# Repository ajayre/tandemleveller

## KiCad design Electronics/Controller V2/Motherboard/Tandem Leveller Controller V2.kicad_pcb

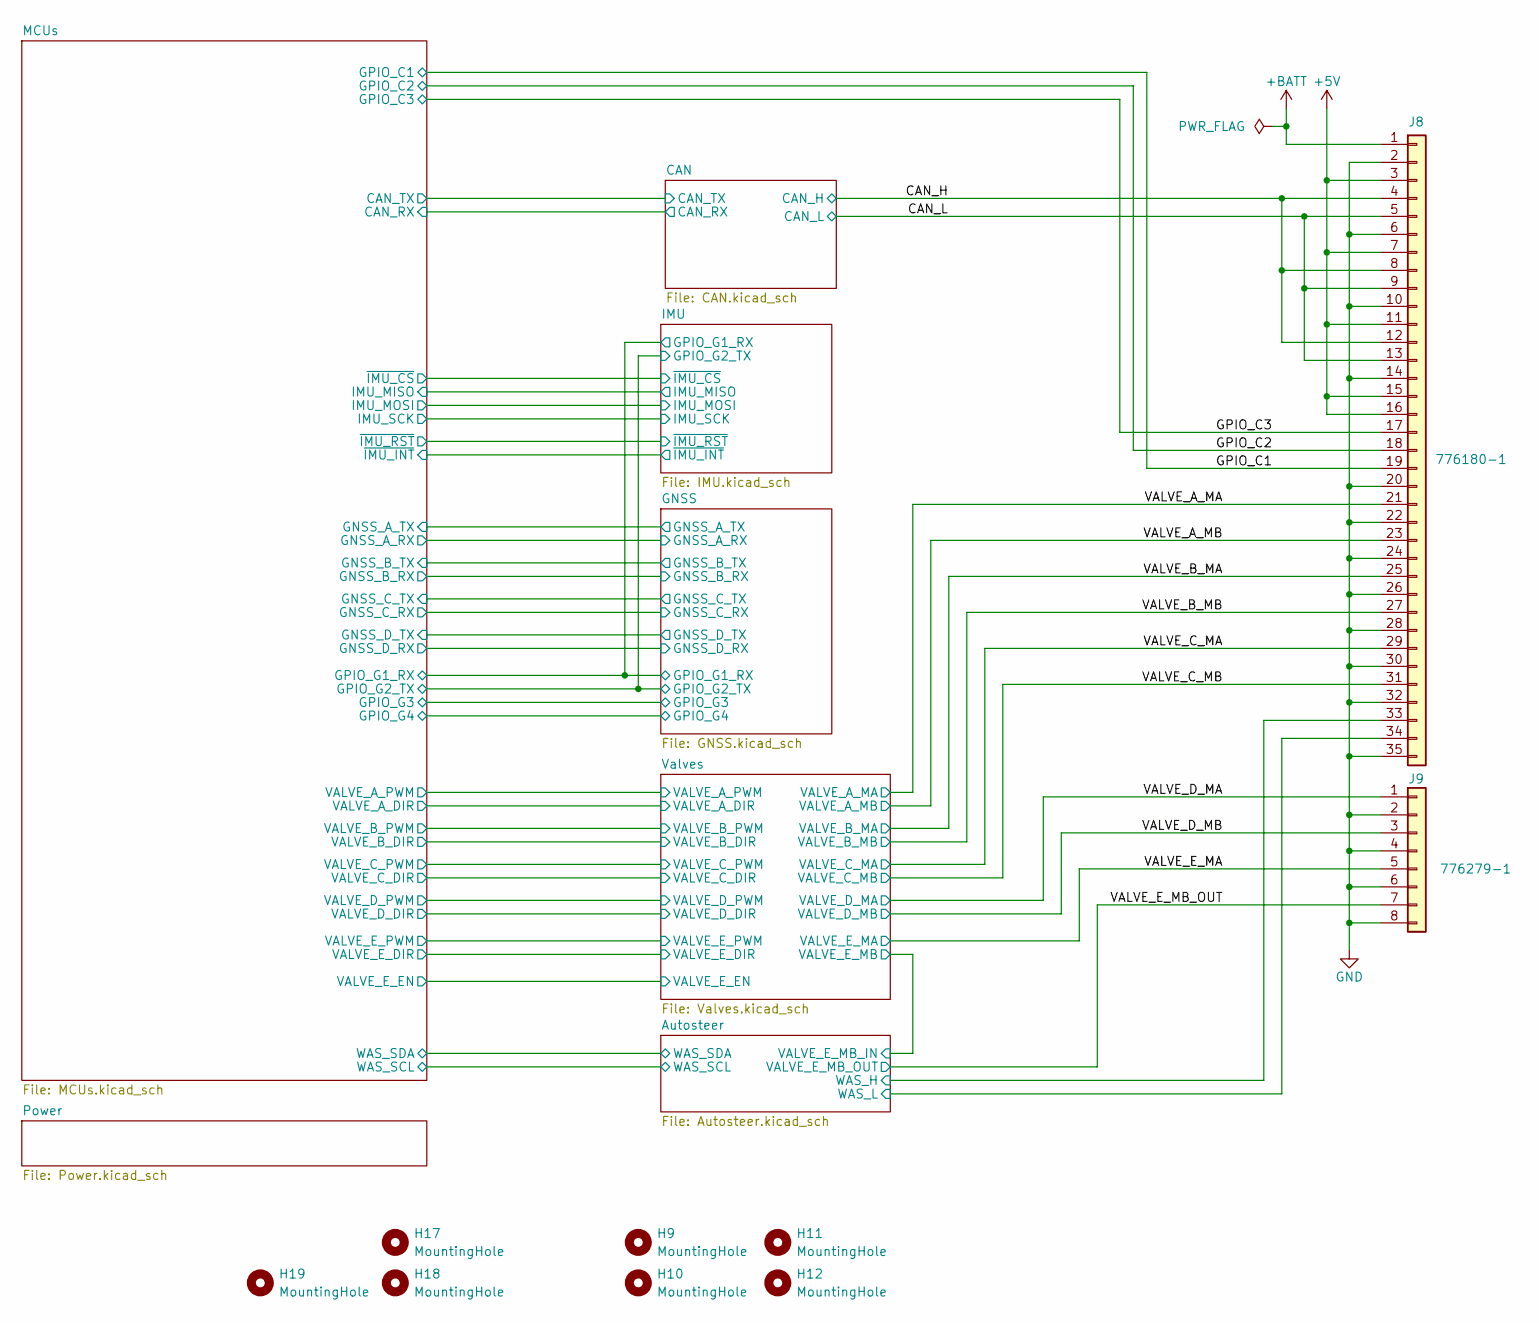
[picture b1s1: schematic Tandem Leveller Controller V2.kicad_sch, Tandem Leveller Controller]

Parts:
H9, H10, H11, H12, H17, H18, H19: MountingHole; MountingHole_4mm
J8: 776180-1; 776180-1 AMPHENOL AMP 35pos
J9: 776279-1; 776279-1 AMPHENOL AMP 8pos

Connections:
+5V: J8.3, J8.7, J8.11, J8.15, J8.16; also elsewhere on the board
+BATT: J8.1; also elsewhere on the board
/Autosteer/WAS_H: J8.33; also elsewhere on the board
/Autosteer/WAS_L: J8.34; also elsewhere on the board
/CAN_H: J8.4, J8.8, J8.12; also elsewhere on the board
/CAN_L: J8.5, J8.9, J8.13; also elsewhere on the board
/GPIO_C1: J8.19; also elsewhere on the board
/GPIO_C2: J8.18; also elsewhere on the board
/GPIO_C3: J8.17; also elsewhere on the board
/VALVE_A_MA: J8.21; also elsewhere on the board
/VALVE_A_MB: J8.23; also elsewhere on the board
/VALVE_B_MA: J8.25; also elsewhere on the board
/VALVE_B_MB: J8.27; also elsewhere on the board
/VALVE_C_MA: J8.29; also elsewhere on the board
/VALVE_C_MB: J8.31; also elsewhere on the board
/VALVE_D_MA: J9.1; also elsewhere on the board
/VALVE_D_MB: J9.3; also elsewhere on the board
/VALVE_E_MA: J9.5; also elsewhere on the board
/VALVE_E_MB_OUT: J9.7; also elsewhere on the board
GND: J8.2, J8.6, J8.10, J8.14, J8.20, J8.22, J8.24, J8.26, J8.28, J8.30, J8.32, J8.35, J9.2, J9.4, J9.6, J9.8; also elsewhere on the board

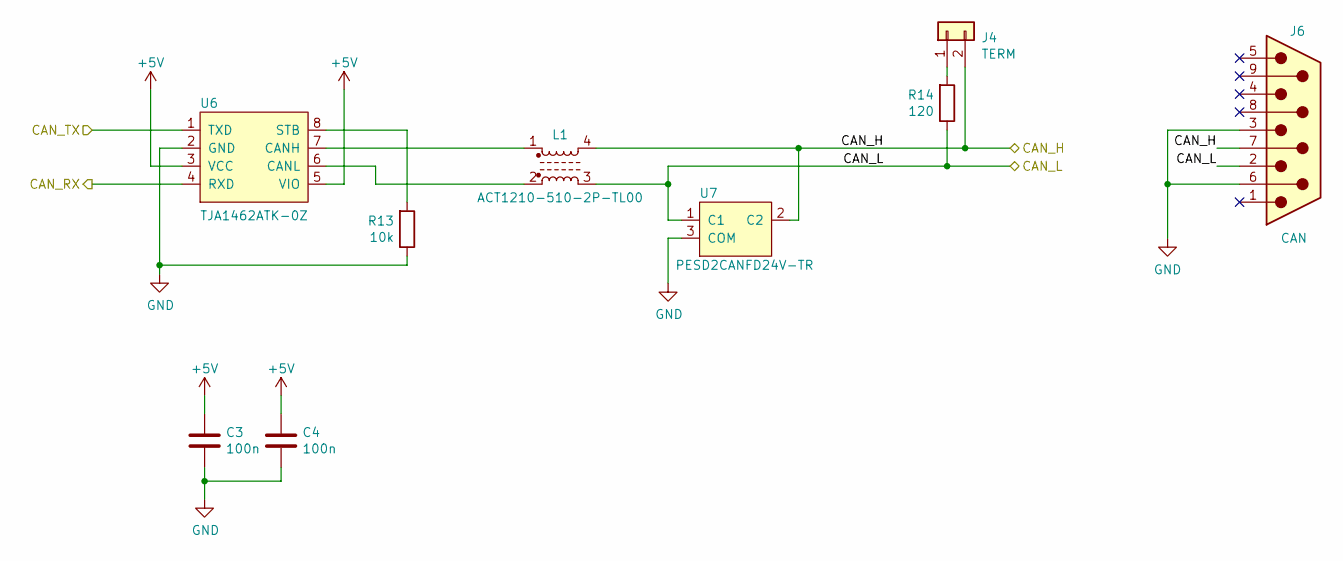
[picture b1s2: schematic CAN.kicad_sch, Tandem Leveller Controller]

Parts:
C3, C4: 100n; C_0805_2012Metric; LCSC C1711
J4: TERM; PinHeader_1x02_P2.54mm_Vertical; LCSC C7494857
J6: CAN; DSUB-9_Male_Vertical_P2.77x2.84mm
L1: ACT1210-510-2P-TL00; LCSC C95572
R13: 10k; R_0805_2012Metric; LCSC C17414
R14: 120; R_0805_2012Metric; LCSC C17437
U6: TJA1462ATK-0Z; HVSON8_0_65mm; LCSC C3229259
U7: PESD2CANFD24V-TR; SOT-23; LCSC C552486

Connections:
+5V: C3.1, C4.1, U6.3 (VCC), U6.5 (VIO); also elsewhere on the board
/CAN/CAN_RX: U6.4 (RXD); also elsewhere on the board
/CAN/CAN_TX: U6.1 (TXD); also elsewhere on the board
/CAN_H: J4.2, J6.7, L1.4, U7.2 (C2); also elsewhere on the board
/CAN_L: J6.2, L1.3, R14.1, U7.1 (C1); also elsewhere on the board
GND: C3.2, C4.2, J6.3, J6.6, R13.1, U6.2 (GND), U7.3 (COM); also elsewhere on the board
unnamed: J4.1, R14.2
unnamed: L1.1, U6.7 (CANH)
unnamed: L1.2, U6.6 (CANL)
unnamed: R13.2, U6.8 (STB)

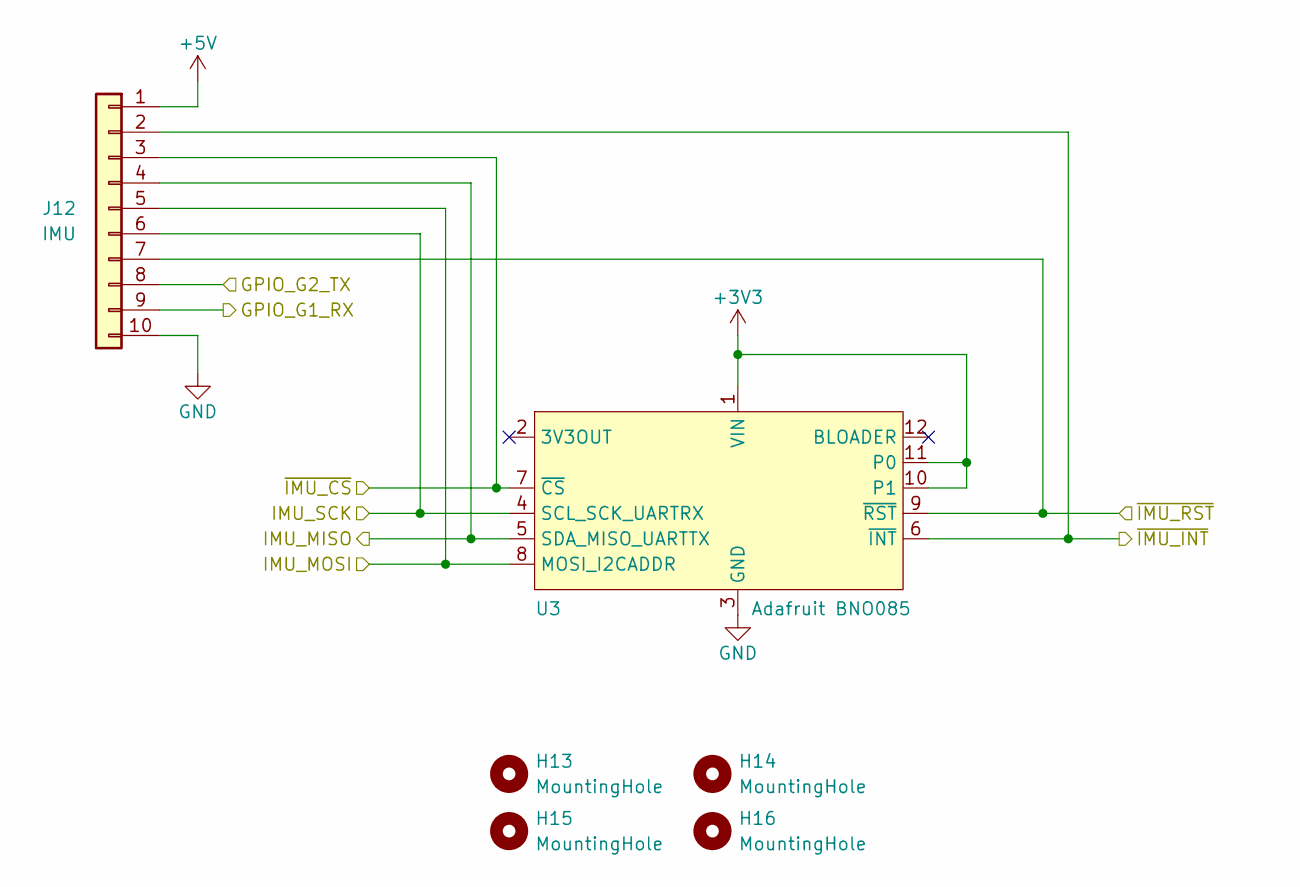
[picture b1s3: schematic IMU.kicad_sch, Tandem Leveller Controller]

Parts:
H13, H14, H15, H16: MountingHole; MountingHole_3.2mm_M3
J12: IMU; JST_PH_B10B-PH-K_1x10_P2.00mm_Vertical
U3: Adafruit BNO085; Adafruit_BNO085

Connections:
+3V3: U3.1 (VIN), U3.10 (P1), U3.11 (P0); also elsewhere on the board
+5V: J12.1; also elsewhere on the board
/GNSS/GPIO_G1: J12.9; also elsewhere on the board
/GNSS/GPIO_G2: J12.8; also elsewhere on the board
/IMU/IMU_MISO: J12.4, U3.5 (SDA_MISO_UARTTX); also elsewhere on the board
/IMU/IMU_MOSI: J12.5, U3.8 (MOSI_I2CADDR); also elsewhere on the board
/IMU/IMU_SCK: J12.6, U3.4 (SCL_SCK_UARTRX); also elsewhere on the board
/IMU/~IMU_CS: J12.3, U3.7 (~CS); also elsewhere on the board
/IMU/~IMU_INT: J12.2, U3.6 (~INT); also elsewhere on the board
/IMU/~IMU_RST: J12.7, U3.9 (~RST); also elsewhere on the board
GND: J12.10, U3.3 (GND); also elsewhere on the board

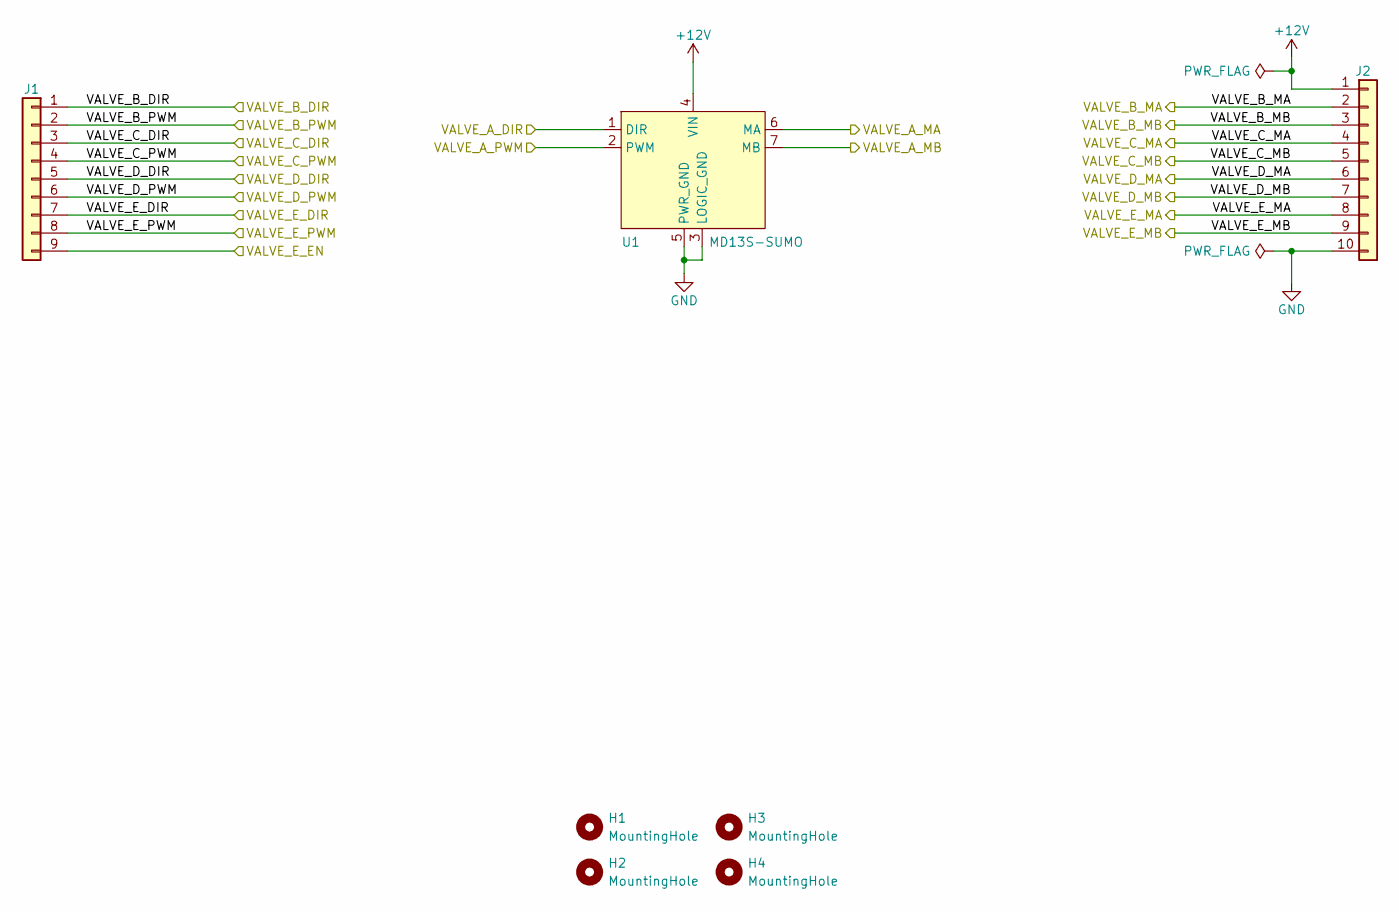
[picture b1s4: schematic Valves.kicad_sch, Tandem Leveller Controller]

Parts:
H1, H2, H3, H4: MountingHole; MountingHole_6.4mm_M6
J1: Conn_01x08; JST_PH_B9B-PH-K_1x09_P2.00mm_Vertical
J2: Conn_01x10; JST_XH_B10B-XH-A_1x10_P2.50mm_Vertical
U1: MD13S-SUMO

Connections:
+12V: J2.1, U1.4 (VIN); also elsewhere on the board
/MCUs/VALVE_A_DIR: U1.1 (DIR); also elsewhere on the board
/MCUs/VALVE_A_PWM: U1.2 (PWM); also elsewhere on the board
/MCUs/VALVE_E_EN: J1.9; also elsewhere on the board
/VALVE_A_MA: U1.6 (MA); also elsewhere on the board
/VALVE_A_MB: U1.7 (MB); also elsewhere on the board
/VALVE_B_MA: J2.2; also elsewhere on the board
/VALVE_B_MB: J2.3; also elsewhere on the board
/VALVE_C_MA: J2.4; also elsewhere on the board
/VALVE_C_MB: J2.5; also elsewhere on the board
/VALVE_D_MA: J2.6; also elsewhere on the board
/VALVE_D_MB: J2.7; also elsewhere on the board
/VALVE_E_MA: J2.8; also elsewhere on the board
/Valves/VALVE_B_DIR: J1.1; also elsewhere on the board
/Valves/VALVE_B_PWM: J1.2; also elsewhere on the board
/Valves/VALVE_C_DIR: J1.3; also elsewhere on the board
/Valves/VALVE_C_PWM: J1.4; also elsewhere on the board
/Valves/VALVE_D_DIR: J1.5; also elsewhere on the board
/Valves/VALVE_D_PWM: J1.6; also elsewhere on the board
/Valves/VALVE_E_DIR: J1.7; also elsewhere on the board
/Valves/VALVE_E_MB: J2.9; also elsewhere on the board
/Valves/VALVE_E_PWM: J1.8; also elsewhere on the board
GND: J2.10, U1.3 (LOGIC_GND), U1.5 (PWR_GND); also elsewhere on the board

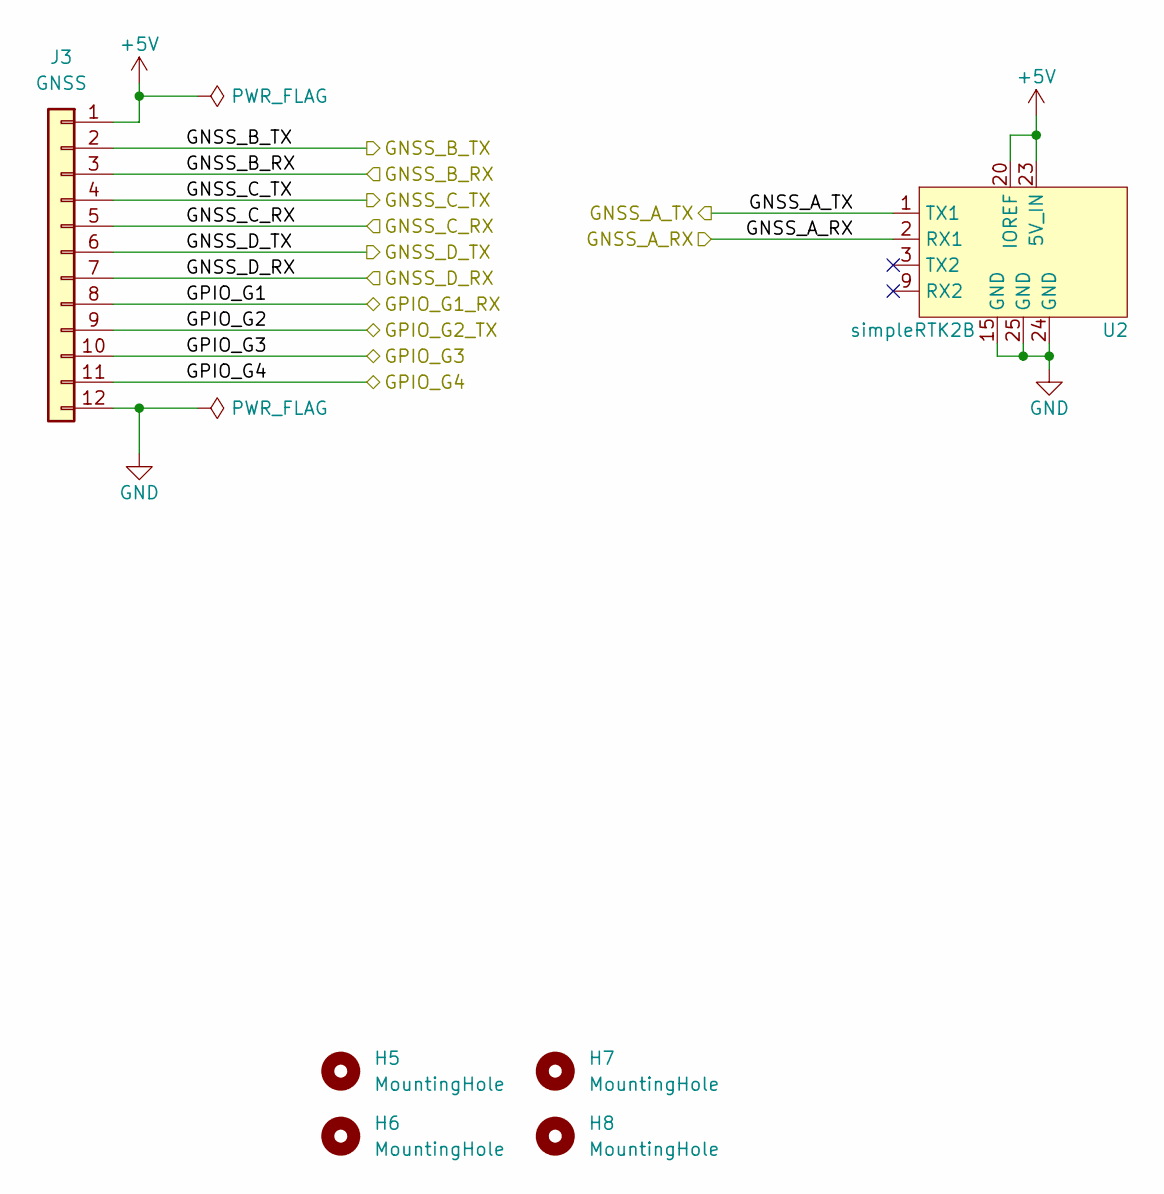
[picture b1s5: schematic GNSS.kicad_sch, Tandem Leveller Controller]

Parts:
H5, H6, H7, H8: MountingHole; MountingHole_6.4mm_M6
J3: GNSS; JST_PH_B12B-PH-K_1x12_P2.00mm_Vertical
U2: simpleRTK2B

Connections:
+5V: J3.1, U2.20 (IOREF), U2.23 (5V_IN); also elsewhere on the board
/GNSS/GNSS_A_RX: U2.2 (RX1); also elsewhere on the board
/GNSS/GNSS_A_TX: U2.1 (TX1); also elsewhere on the board
/GNSS/GNSS_B_RX: J3.3; also elsewhere on the board
/GNSS/GNSS_B_TX: J3.2; also elsewhere on the board
/GNSS/GNSS_C_RX: J3.5; also elsewhere on the board
/GNSS/GNSS_C_TX: J3.4; also elsewhere on the board
/GNSS/GNSS_D_RX: J3.7; also elsewhere on the board
/GNSS/GNSS_D_TX: J3.6; also elsewhere on the board
/GNSS/GPIO_G1: J3.8; also elsewhere on the board
/GNSS/GPIO_G2: J3.9; also elsewhere on the board
/GNSS/GPIO_G3: J3.10; also elsewhere on the board
/GNSS/GPIO_G4: J3.11; also elsewhere on the board
GND: J3.12, U2.15 (GND), U2.24 (GND), U2.25 (GND); also elsewhere on the board

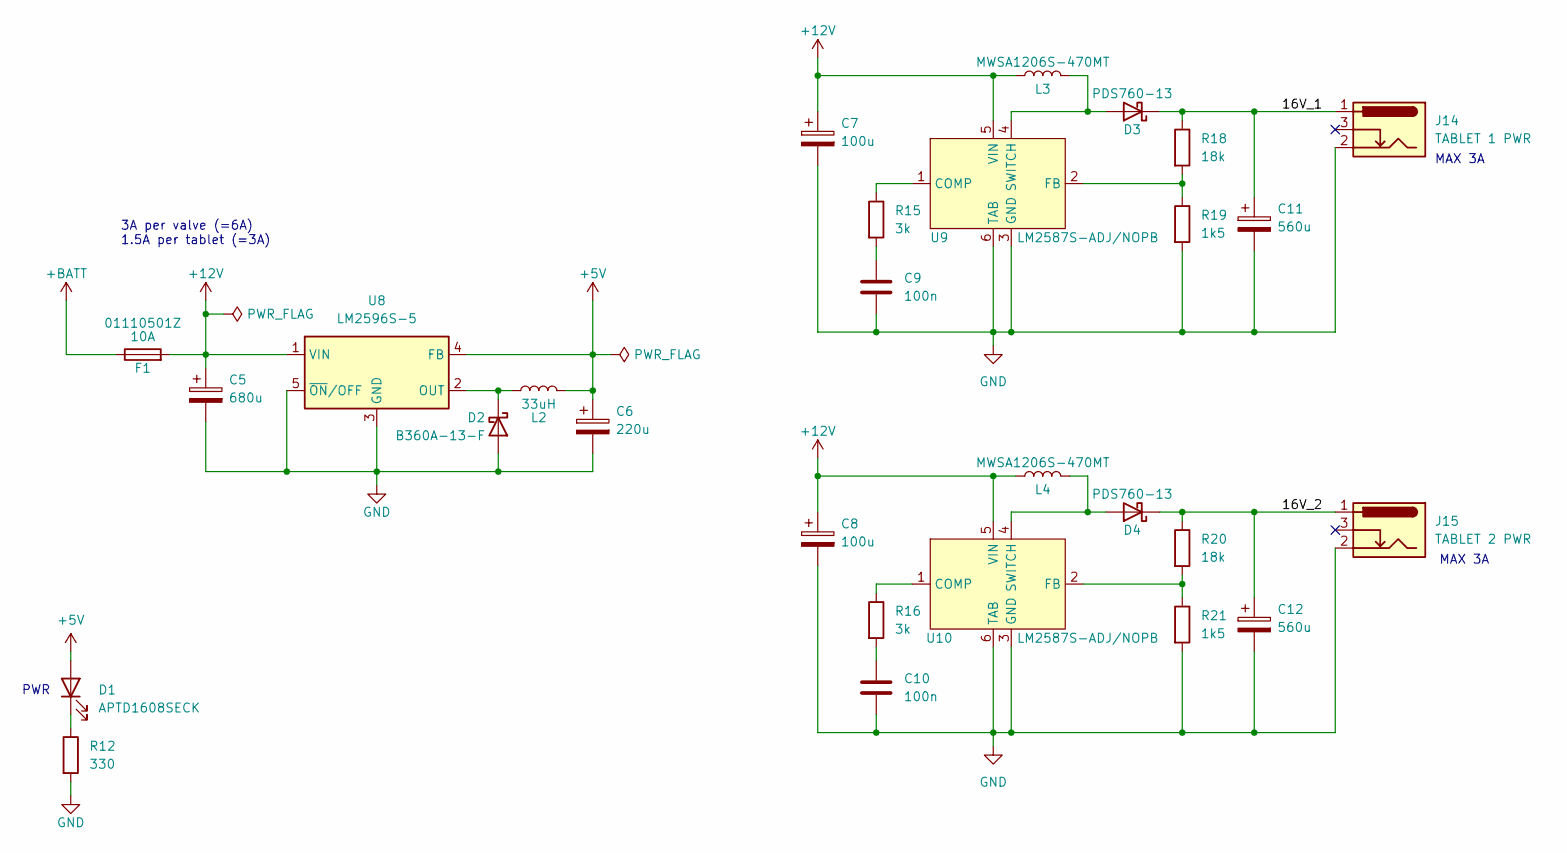
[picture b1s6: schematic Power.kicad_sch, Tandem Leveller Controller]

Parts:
C5: 680u; CP_Elec_10x10.5; LCSC C50456
C6: 220u; CP_Elec_8x6.5; LCSC C3340
C7, C8: 100u; CP_Elec_6.3x5.9; LCSC C340733
C9, C10: 100n; C_0805_2012Metric; LCSC C1711
C11, C12: 560u; CP_Elec_10x10.5; LCSC C1984785
D1: APTD1608SECK; D_0603_1608Metric; LCSC C5879220
D2: B360A-13-F; D_SMA; LCSC C6807778
D3, D4: PDS760-13; D_PowerDI-5; LCSC C3018534
F1: 10A; 5x20 Fuse Holder; LCSC C151075
J14: TABLET 1 PWR; BarrelJack_Wuerth_6941xx301002; LCSC C5441017
J15: TABLET 2 PWR; BarrelJack_Wuerth_6941xx301002; LCSC C5441017
L2: 33uH; MWSA0603S-330MT; LCSC C408454
L3, L4: MWSA1206S-470MT; LCSC C408531
R12: 330; R_0805_2012Metric; LCSC C17630
R15, R16: 3k; R_0805_2012Metric; LCSC C17661
R18, R20: 18k; R_0805_2012Metric; LCSC C17506
R19, R21: 1k5; R_0805_2012Metric; LCSC C4310
U8: LM2596S-5; TO-263-5_TabPin3; LCSC C5276750
U9, U10: LM2587S-ADJ/NOPB; TO-263-5_TabPin6; LCSC C1355343

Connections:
+5V: C6.1, D1.2 (A), L2.2, U8.4 (FB); also elsewhere on the board
+12V: C5.1, C7.1, C8.1, F1.2, L3.1, L4.1, U8.1 (VIN), U9.5 (VIN), U10.5 (VIN); also elsewhere on the board
+BATT: F1.1; also elsewhere on the board
/Power/16V_1: C11.1, D3.1 (K), J14.1, R18.1
/Power/16V_2: C12.1, D4.1 (K), J15.1, R20.1
GND: C5.2, C6.2, C7.2, C8.2, C9.2, C10.2, C11.2, C12.2, D2.2 (A), J14.2, J15.2, R12.2, R19.2, R21.2, U8.3 (GND), U8.5 (~ON/OFF), U9.3 (GND), U9.6 (TAB), U10.3 (GND), U10.6 (TAB); also elsewhere on the board
unnamed: C9.1, R15.2
unnamed: C10.1, R16.2
unnamed: D1.1 (K), R12.1
unnamed: D2.1 (K), L2.1, U8.2 (OUT)
unnamed: D3.2 (A), L3.2, U9.4 (SWITCH)
unnamed: D4.2 (A), L4.2, U10.4 (SWITCH)
unnamed: R15.1, U9.1 (COMP)
unnamed: R18.2, R19.1, U9.2 (FB)
unnamed: R16.1, U10.1 (COMP)
unnamed: R20.2, R21.1, U10.2 (FB)

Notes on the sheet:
PWR
3A per valve (=6A) 1.5A per tablet (=3A)
MAX 3A

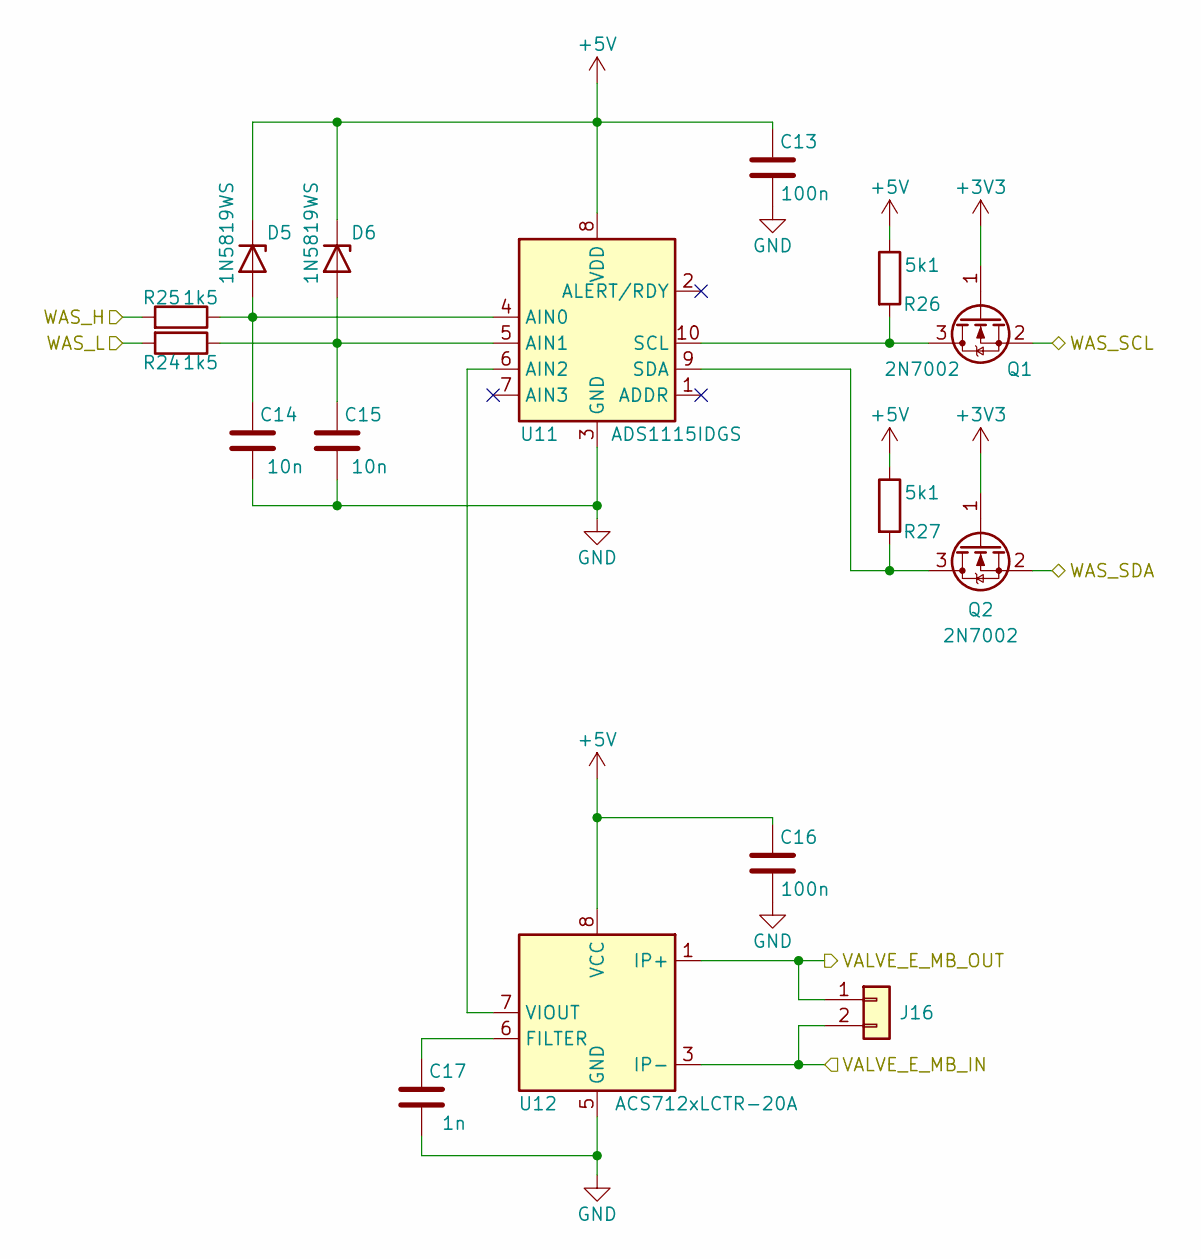
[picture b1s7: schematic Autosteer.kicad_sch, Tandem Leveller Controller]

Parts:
C13, C16: 100n; C_0805_2012Metric; LCSC C1711
C14, C15: 10n; C_0805_2012Metric
C17: 1n; C_0805_2012Metric
D5, D6: 1N5819WS; D_SOD-323; LCSC C191023
J16: PinHeader_1x02_P2.54mm_Vertical; LCSC C7494857
Q1, Q2: 2N7002; SOT-23
R24, R25: 1k5; R_0805_2012Metric
R26, R27: 5k1; R_0805_2012Metric
U11: ADS1115IDGS; TSSOP-10_3x3mm_P0.5mm
U12: ACS712xLCTR-20A; SOIC-8_3.9x4.9mm_P1.27mm

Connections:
+3V3: Q1.1 (G), Q2.1 (G); also elsewhere on the board
+5V: C13.2, C16.2, D5.1 (K), D6.1 (K), R26.1, R27.1, U11.8 (VDD), U12.8 (VCC); also elsewhere on the board
/Autosteer/WAS_H: R25.2; also elsewhere on the board
/Autosteer/WAS_L: R24.2; also elsewhere on the board
/Autosteer/WAS_SCL: Q1.2 (S); also elsewhere on the board
/Autosteer/WAS_SDA: Q2.2 (S); also elsewhere on the board
/VALVE_E_MB_OUT: J16.1, U12.1 (IP+), U12.2 (IP+); also elsewhere on the board
/Valves/VALVE_E_MB: J16.2, U12.3 (IP-), U12.4 (IP-); also elsewhere on the board
GND: C13.1, C14.1, C15.1, C16.1, C17.1, U11.3 (GND), U12.5 (GND); also elsewhere on the board
unnamed: C14.2, D5.2 (A), R25.1, U11.4 (AIN0)
unnamed: C15.2, D6.2 (A), R24.1, U11.5 (AIN1)
unnamed: Q1.3 (D), R26.2, U11.10 (SCL)
unnamed: Q2.3 (D), R27.2, U11.9 (SDA)
unnamed: U11.6 (AIN2), U12.7 (VIOUT)
unnamed: C17.2, U12.6 (FILTER)

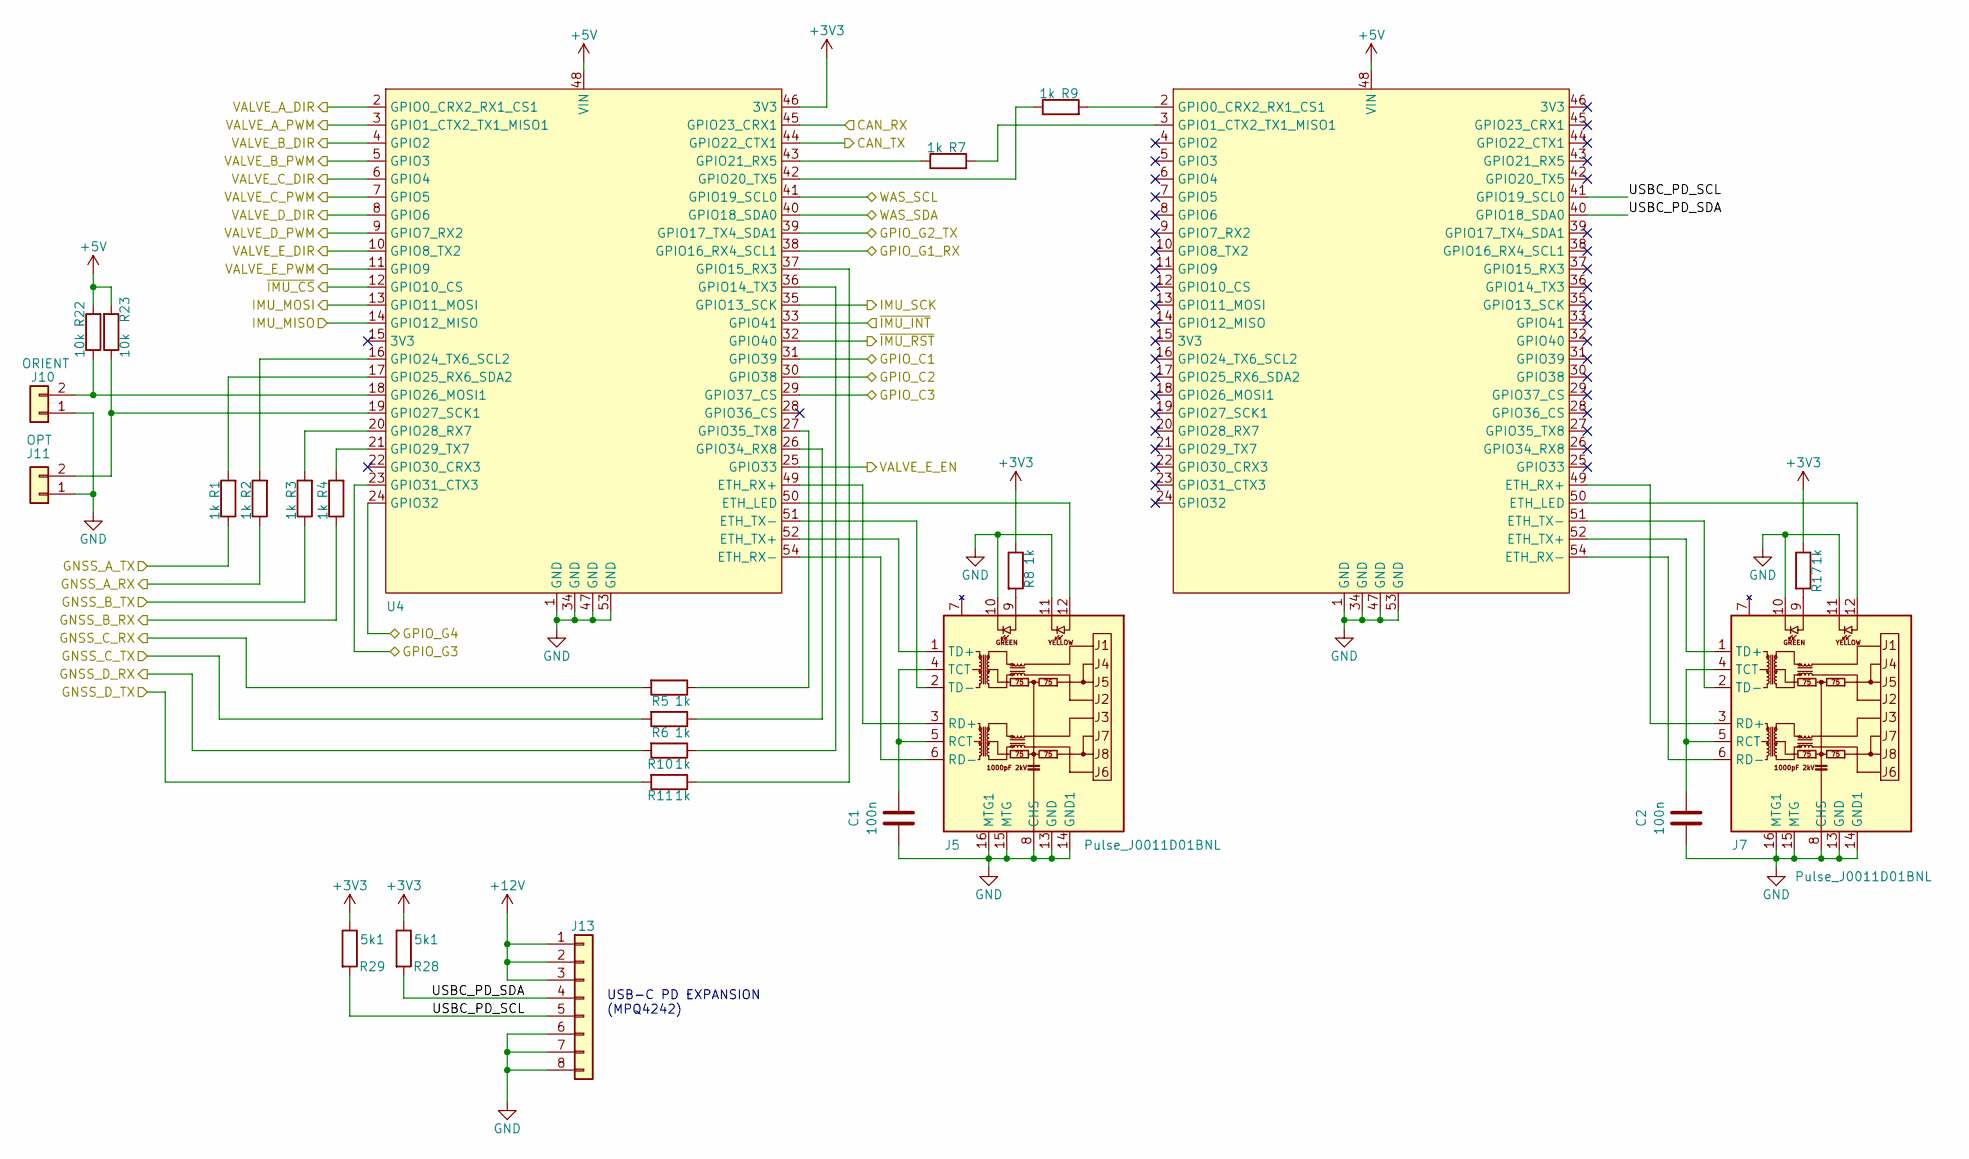
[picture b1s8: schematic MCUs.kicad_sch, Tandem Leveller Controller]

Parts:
C1, C2: 100n; C_0805_2012Metric; LCSC C1711
J5, J7: Pulse_J0011D01BNL; LCSC C581368
J10: ORIENT; PinHeader_1x02_P2.54mm_Vertical; LCSC C7494857
J11: OPT; PinHeader_1x02_P2.54mm_Vertical; LCSC C7494857
J13: Conn_01x10; JST_XH_B8B-XH-A_1x08_P2.50mm_Vertical
R1, R2, R3, R4, R5, R6, R7, R8, R9, R10, R11, R17: 1k; R_0805_2012Metric; LCSC C17513
R22, R23: 10k; R_0805_2012Metric; LCSC C17513
R28, R29: 5k1; R_0805_2012Metric
U4, U5: Teensy_4.1

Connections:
+3V3: R8.1, R17.1, R28.1, R29.1, U4.46 (3V3); also elsewhere on the board
+5V: R22.2, R23.2, U4.48 (VIN), U5.48 (VIN); also elsewhere on the board
+12V: J13.1, J13.2, J13.3; also elsewhere on the board
/Autosteer/WAS_SCL: U4.41 (GPIO19_SCL0); also elsewhere on the board
/Autosteer/WAS_SDA: U4.40 (GPIO18_SDA0); also elsewhere on the board
/CAN/CAN_RX: U4.45 (GPIO23_CRX1); also elsewhere on the board
/CAN/CAN_TX: U4.44 (GPIO22_CTX1); also elsewhere on the board
/GNSS/GNSS_A_RX: R2.1; also elsewhere on the board
/GNSS/GNSS_A_TX: R1.1; also elsewhere on the board
/GNSS/GNSS_B_RX: R4.1; also elsewhere on the board
/GNSS/GNSS_B_TX: R3.1; also elsewhere on the board
/GNSS/GNSS_C_RX: R5.2; also elsewhere on the board
/GNSS/GNSS_C_TX: R6.2; also elsewhere on the board
/GNSS/GNSS_D_RX: R10.2; also elsewhere on the board
/GNSS/GNSS_D_TX: R11.2; also elsewhere on the board
/GNSS/GPIO_G1: U4.38 (GPIO16_RX4_SCL1); also elsewhere on the board
/GNSS/GPIO_G2: U4.39 (GPIO17_TX4_SDA1); also elsewhere on the board
/GNSS/GPIO_G3: U4.23 (GPIO31_CTX3); also elsewhere on the board
/GNSS/GPIO_G4: U4.24 (GPIO32); also elsewhere on the board
/GPIO_C1: U4.31 (GPIO39); also elsewhere on the board
/GPIO_C2: U4.30 (GPIO38); also elsewhere on the board
/GPIO_C3: U4.29 (GPIO37_CS); also elsewhere on the board
/IMU/IMU_MISO: U4.14 (GPIO12_MISO); also elsewhere on the board
/IMU/IMU_MOSI: U4.13 (GPIO11_MOSI); also elsewhere on the board
/IMU/IMU_SCK: U4.35 (GPIO13_SCK); also elsewhere on the board
/IMU/~IMU_CS: U4.12 (GPIO10_CS); also elsewhere on the board
/IMU/~IMU_INT: U4.33 (GPIO41); also elsewhere on the board
/IMU/~IMU_RST: U4.32 (GPIO40); also elsewhere on the board
/MCUs/USBC_PD_SCL: J13.5, R29.2, U5.41 (GPIO19_SCL0)
/MCUs/USBC_PD_SDA: J13.4, R28.2, U5.40 (GPIO18_SDA0)
/MCUs/VALVE_A_DIR: U4.2 (GPIO0_CRX2_RX1_CS1); also elsewhere on the board
/MCUs/VALVE_A_PWM: U4.3 (GPIO1_CTX2_TX1_MISO1); also elsewhere on the board
/MCUs/VALVE_E_EN: U4.25 (GPIO33); also elsewhere on the board
/Valves/VALVE_B_DIR: U4.4 (GPIO2); also elsewhere on the board
/Valves/VALVE_B_PWM: U4.5 (GPIO3); also elsewhere on the board
/Valves/VALVE_C_DIR: U4.6 (GPIO4); also elsewhere on the board
/Valves/VALVE_C_PWM: U4.7 (GPIO5); also elsewhere on the board
/Valves/VALVE_D_DIR: U4.8 (GPIO6); also elsewhere on the board
/Valves/VALVE_D_PWM: U4.9 (GPIO7_RX2); also elsewhere on the board
/Valves/VALVE_E_DIR: U4.10 (GPIO8_TX2); also elsewhere on the board
/Valves/VALVE_E_PWM: U4.11 (GPIO9); also elsewhere on the board
GND: C1.1, C2.1, J5.8 (CHS), J5.10, J5.11, J5.13 (GND), J5.14 (GND1), J5.15 (MTG), J5.16 (MTG1), J7.8 (CHS), J7.10, J7.11, J7.13 (GND), J7.14 (GND1), J7.15 (MTG), J7.16 (MTG1), J10.1, J11.1, J13.6, J13.7, J13.8, U4.1 (GND), U4.34 (GND), U4.47 (GND), U4.53 (GND), U5.1 (GND), U5.34 (GND), U5.47 (GND), U5.53 (GND); also elsewhere on the board
unnamed: J5.9, R8.2
unnamed: C1.2, J5.4 (TCT), J5.5 (RCT)
unnamed: J5.3 (RD+), U4.49 (ETH_RX+)
unnamed: J5.6 (RD-), U4.54 (ETH_RX-)
unnamed: J5.1 (TD+), U4.52 (ETH_TX+)
unnamed: J5.2 (TD-), U4.51 (ETH_TX-)
unnamed: J7.9, R17.2
unnamed: C2.2, J7.4 (TCT), J7.5 (RCT)
unnamed: J7.3 (RD+), U5.49 (ETH_RX+)
unnamed: J7.6 (RD-), U5.54 (ETH_RX-)
unnamed: J7.1 (TD+), U5.52 (ETH_TX+)
unnamed: J7.2 (TD-), U5.51 (ETH_TX-)
unnamed: J10.2, R22.1, U4.18 (GPIO26_MOSI1)
unnamed: J11.2, R23.1, U4.19 (GPIO27_SCK1)
unnamed: J5.12, U4.50 (ETH_LED)
unnamed: R10.1, U4.36 (GPIO14_TX3)
unnamed: R11.1, U4.37 (GPIO15_RX3)
unnamed: R9.1, U4.42 (GPIO20_TX5)
unnamed: R7.1, U4.43 (GPIO21_RX5)
unnamed: R2.2, U4.16 (GPIO24_TX6_SCL2)
unnamed: R1.2, U4.17 (GPIO25_RX6_SDA2)
unnamed: R3.2, U4.20 (GPIO28_RX7)
unnamed: R4.2, U4.21 (GPIO29_TX7)
unnamed: R6.1, U4.26 (GPIO34_RX8)
unnamed: R5.1, U4.27 (GPIO35_TX8)
unnamed: J7.12, U5.50 (ETH_LED)
unnamed: R9.2, U5.2 (GPIO0_CRX2_RX1_CS1)
unnamed: R7.2, U5.3 (GPIO1_CTX2_TX1_MISO1)

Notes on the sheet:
USB-C PD EXPANSION (MPQ4242)

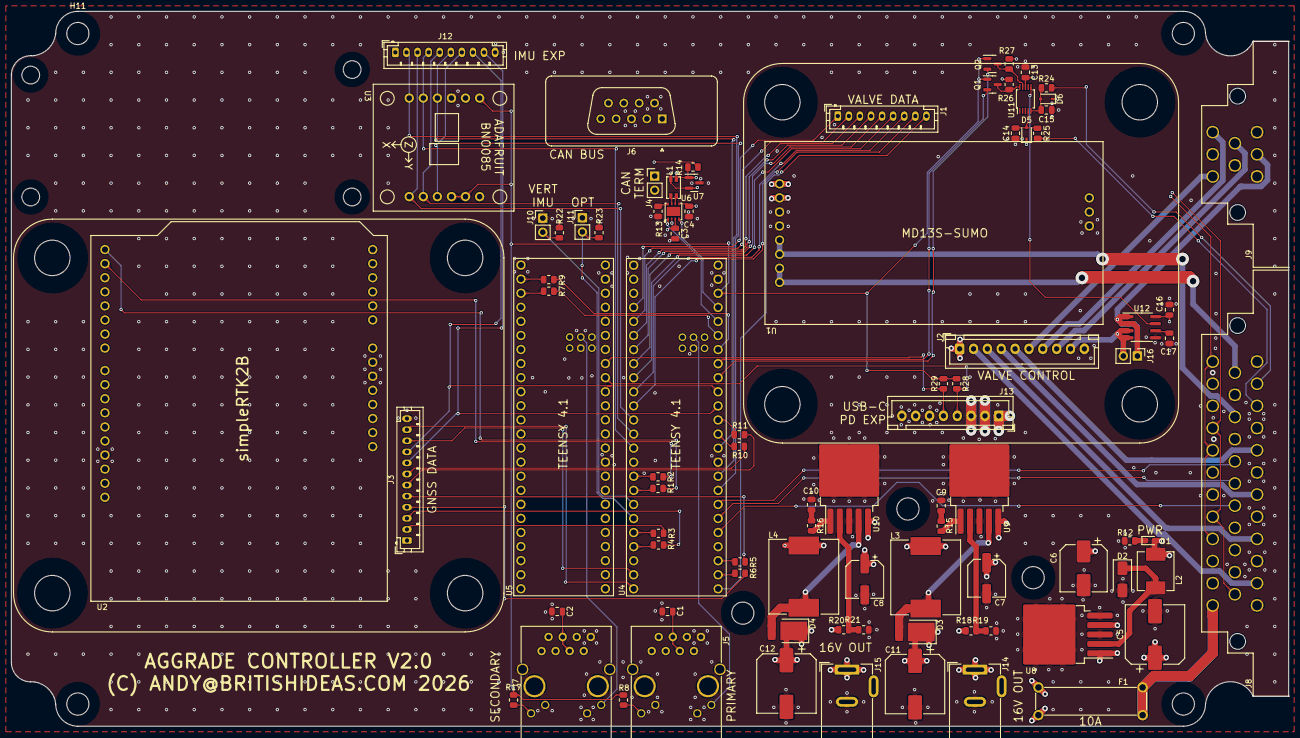
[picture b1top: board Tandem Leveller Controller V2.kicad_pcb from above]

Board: 6 copper layers, 230.5 x 129.0 mm, 106 parts (0 on the bottom side), 108 nets.

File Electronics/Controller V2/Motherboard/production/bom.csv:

Designator,Footprint,Quantity,Value,LCSC Part #
"C1, C10, C13, C16, C2, C3, C4, C9",0805,8,100n,C1711
"C11, C12",CP_Elec_10x10.5,2,560u,C1984785
"C14, C15",0805,2,10n,
C17,0805,1,1n,
C5,CP_Elec_10x10.5,1,680u,C50456
C6,CP_Elec_8x6.5,1,220u,C3340
"C7, C8",CP_Elec_6.3x5.9,2,1729034,C340733
D1,0603,1,APTD1608SECK,C5879220
D2,D_SMA,1,B360A-13-F,C6807778
"D3, D4",D_PowerDI-5,2,PDS760-13,C3018534
"D5, D6",D_SOD-323,2,1N5819WS,C191023
F1,5x20 Fuse Holder,1,10A,C151075
"H1, H2, H3, H4, H5, H6, H7, H8",MountingHole_6.4mm_M6,8,MountingHole,
"H10, H11, H12, H17, H18, H19, H9",MountingHole_4mm,7,MountingHole,
"H13, H14, H15, H16",MountingHole_3.2mm_M3,4,MountingHole,
J1,JST_PH_B9B-PH-K_1x09_P2.00mm_Vertical,1,Conn_01x08,
J10,PinHeader_1x02_P2.54mm_Vertical,1,ORIENT,C7494857
J11,PinHeader_1x02_P2.54mm_Vertical,1,OPT,C7494857
J12,JST_PH_B10B-PH-K_1x10_P2.00mm_Vertical,1,IMU,
J13,JST_XH_B8B-XH-A_1x08_P2.50mm_Vertical,1,Conn_01x10,
J14,BarrelJack_Wuerth_6941xx301002,1,TABLET 1 PWR,C5441017
J15,BarrelJack_Wuerth_6941xx301002,1,TABLET 2 PWR,C5441017
J16,PinHeader_1x02_P2.54mm_Vertical,1,~,C7494857
J2,JST_XH_B10B-XH-A_1x10_P2.50mm_Vertical,1,Conn_01x10,
J3,JST_PH_B12B-PH-K_1x12_P2.00mm_Vertical,1,GNSS,
J4,PinHeader_1x02_P2.54mm_Vertical,1,TERM,C7494857
"J5, J7",Pulse_J0011D01BNL,2,Pulse_J0011D01BNL,C581368
J6,DSUB-9_Male_Vertical_P2.77x2.84mm,1,CAN,
J8,776180-1 AMPHENOL AMP 35pos,1,776180-1,
J9,776279-1 AMPHENOL AMP 8pos,1,776279-1,
L1,ACT1210-510-2P-TL00,1,ACT1210-510-2P-TL00,C95572
L2,MWSA0603S-330MT,1,33uH,C408454
"L3, L4",MWSA1206S-470MT,2,MWSA1206S-470MT,C408531
"Q1, Q2",SOT-23,2,2N7002,
"R1, R10, R11, R17, R2, R3, R4, R5, R6, R7, R8, R9",0805,12,1k,C17513
R12,0805,1,330,C17630
R13,0805,1,10k,C17414
R14,0805,1,120,C17437
"R15, R16",0805,2,3k,C17661
"R18, R20",0805,2,18k,C17506
"R19, R21",0805,2,1k5,C4310
"R22, R23",0805,2,10k,C17513
"R24, R25",0805,2,1k5,
"R26, R27, R28, R29",0805,4,5k1,
U1,MD13S-SUMO,1,MD13S-SUMO,
"U10, U9",TO-263-5_TabPin6,2,LM2587S-ADJ/NOPB,C1355343
U11,TSSOP-10_3x3mm_P0.5mm,1,ADS1115IDGS,
U12,SOIC-8_3.9x4.9mm_P1.27mm,1,ACS712xLCTR-20A,
U2,simpleRTK2B,1,simpleRTK2B,
U3,Adafruit_BNO085,1,Adafruit BNO085,
"U4, U5",Teensy_4.1,2,~,
U6,HVSON8_0_65mm,1,TJA1462ATK-0Z,C3229259
U7,SOT-23,1,PESD2CANFD24V-TR,C552486
U8,TO-263-5_TabPin3,1,LM2596S-5,C5276750

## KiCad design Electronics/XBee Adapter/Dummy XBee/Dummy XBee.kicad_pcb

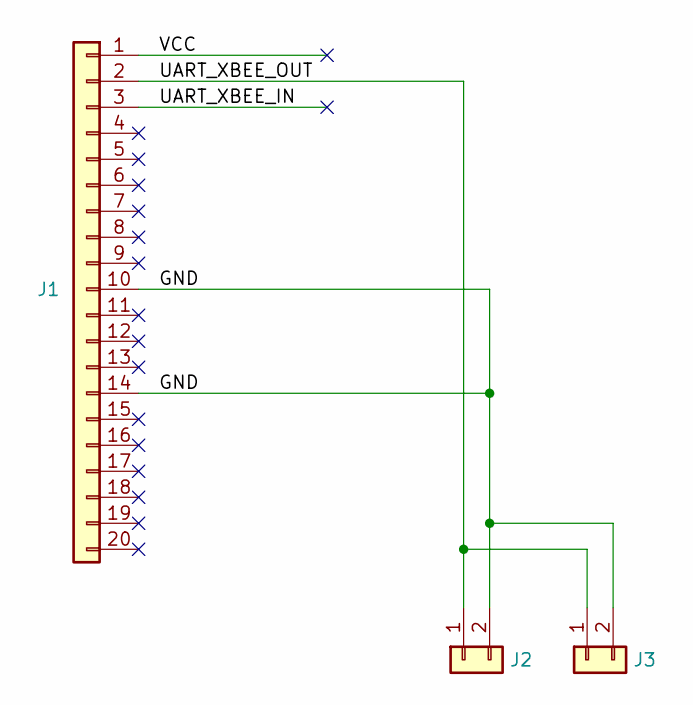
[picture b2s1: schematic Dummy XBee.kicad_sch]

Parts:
J1: Conn_01x20; XBee 3 TH
J2, J3: Conn_01x04; JST_PH_B2B-PH-K_1x02_P2.00mm_Vertical

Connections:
/GND: J1.10, J1.14, J2.2, J3.2
/UART_XBEE_IN: J1.3
/UART_XBEE_OUT: J1.2, J2.1, J3.1
/VCC: J1.1
